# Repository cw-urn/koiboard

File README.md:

# koiboard
> What is this?
- Koiboard is a 40% ortholinear mechanical low-profile keyboard.
> How do you use it?
- Well you know how to you a keyboard, right? This one just has its keys aligned differently!
> Why did I make this?
- Honestly, I saw the simplicity of the [XYZ Work Board](https://worklouder.cc/xyz-work-board-2), plus other boards, and thought I could make it myself.

<hr>

<hr>

## 3D render

## PCB
[Open online PCB viewer](https://kicanvas.org/?repo=https%3A%2F%2Fgithub.com%2Fcw-urn%2Fkoiboard%2Ftree%2Fmain%2Fpcb)

### Layer 1

### Layer 2

### PCB 3D render

### Final PCB

### Schematic
This is split up into multiple pages. Check pcb/exports/koiboard.pdf!

## Gallery

More images in assets/webp!!!

## PCB BOM

| Designator | Quantity | Value | LCSC Part # | JLCPCB Link |
| :---: | :---: | :---: | :---: | :---: |
| BOOT1, RST1 | 2 | - | C455262 | [Link](https://jlcpcb.com/partdetail/XUNPU-TS_1087S01526/C455262) |
| C1, C2, C14 | 3 | 1u | C14445 | [Link](https://jlcpcb.com/partdetail/15107-CL05A105KP5NNNC/C14445) |
| C4...13 | 10 | 100n | C1525 | [Link](https://jlcpcb.com/partdetail/1877-CL05B104KO5NNNC/C1525) |
| C15, C16 | 2 | 33p | C1562 | [Link](https://jlcpcb.com/partdetail/1914-0402CG330J500NT/C1562) |
| C3 | 1 | 10u | C1691 | [Link](https://jlcpcb.com/partdetail/2043-CL10A106MQ8NNNC/C1691) |
| **D1...49** | 49 | - | C2099 | [Link](https://jlcpcb.com/partdetail/2456-1N4148W/C2099) |
| F1 | 1 | - | C99563 | [Link](https://jlcpcb.com/partdetail/Littelfuse-1206L075THYR/C99563) |
| J1 | 1 | - | C5370443 | [Link](https://jlcpcb.com/partdetail/Korean_HropartsElec-TYPE_C_31_M40/C5370443) |
| **R1...5** | 5 | 5.1k | C25905 | [Link](https://jlcpcb.com/partdetail/26648-0402WGF5101TCE/C25905) |
| R6, R9 | 2 | 1k | C11702 | [Link](https://jlcpcb.com/partdetail/12256-0402WGF1001TCE/C11702) |
| R7, R8 | 2 | 27 | C25100 | [Link](https://jlcpcb.com/partdetail/25843-0402WGF270JTCE/C25100) |
| U1 | 1 | - | C5446 | [Link](https://jlcpcb.com/partdetail/TorexSemicon-XC6206P332MRG/C5446) |
| U2 | 1 | - | C7519 | [Link](https://jlcpcb.com/partdetail/STMicroelectronics-USBLC62SC6/C7519) |
| U3 | 1 | - | C2040 | [Link](https://jlcpcb.com/partdetail/RaspberryPi-RP2040/C2040) |
| U4 | 1 | - | C97521 | [Link](https://jlcpcb.com/partdetail/WinbondElec-W25Q128JVSIQ/C97521) |
| Y1 | 1 | - | C20625731 | [Link](https://jlcpcb.com/partdetail/AbraconLLC-ABM8_272T3/C20625731) |

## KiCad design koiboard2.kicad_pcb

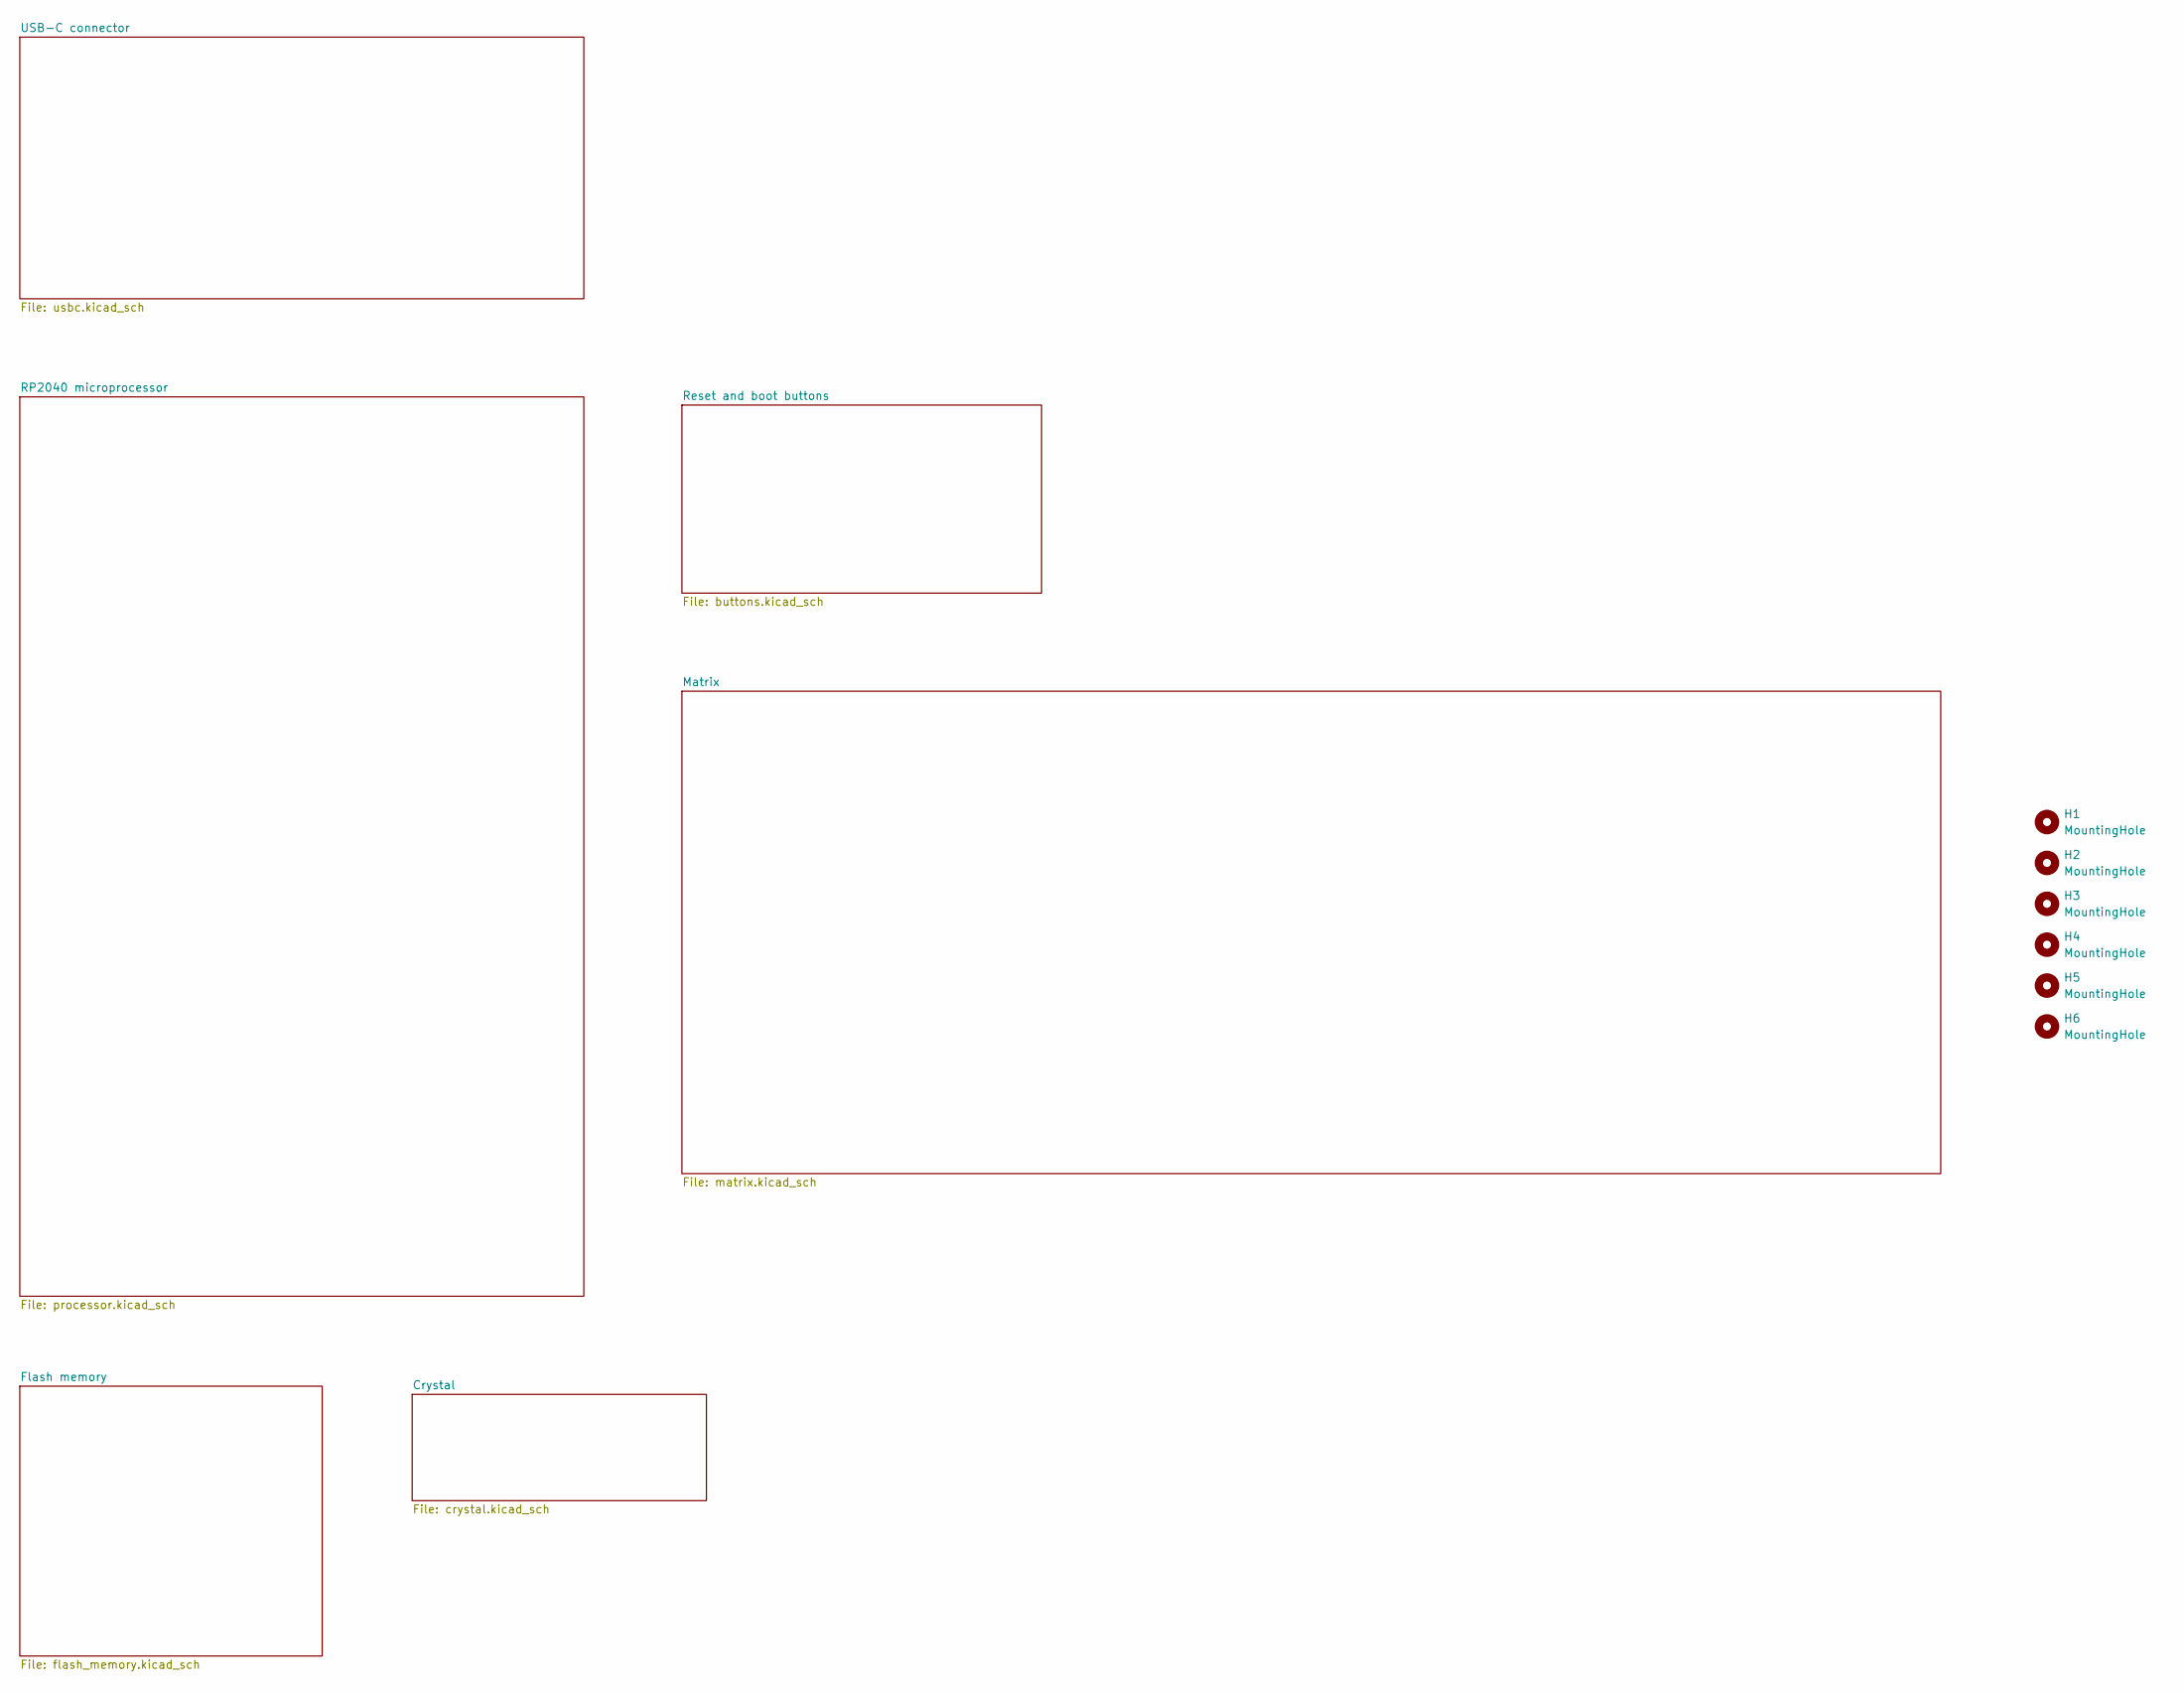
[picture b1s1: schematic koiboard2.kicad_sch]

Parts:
H1, H2, H3, H4, H5, H6: MountingHole; MountingHole_3.2mm_M3_ISO14580

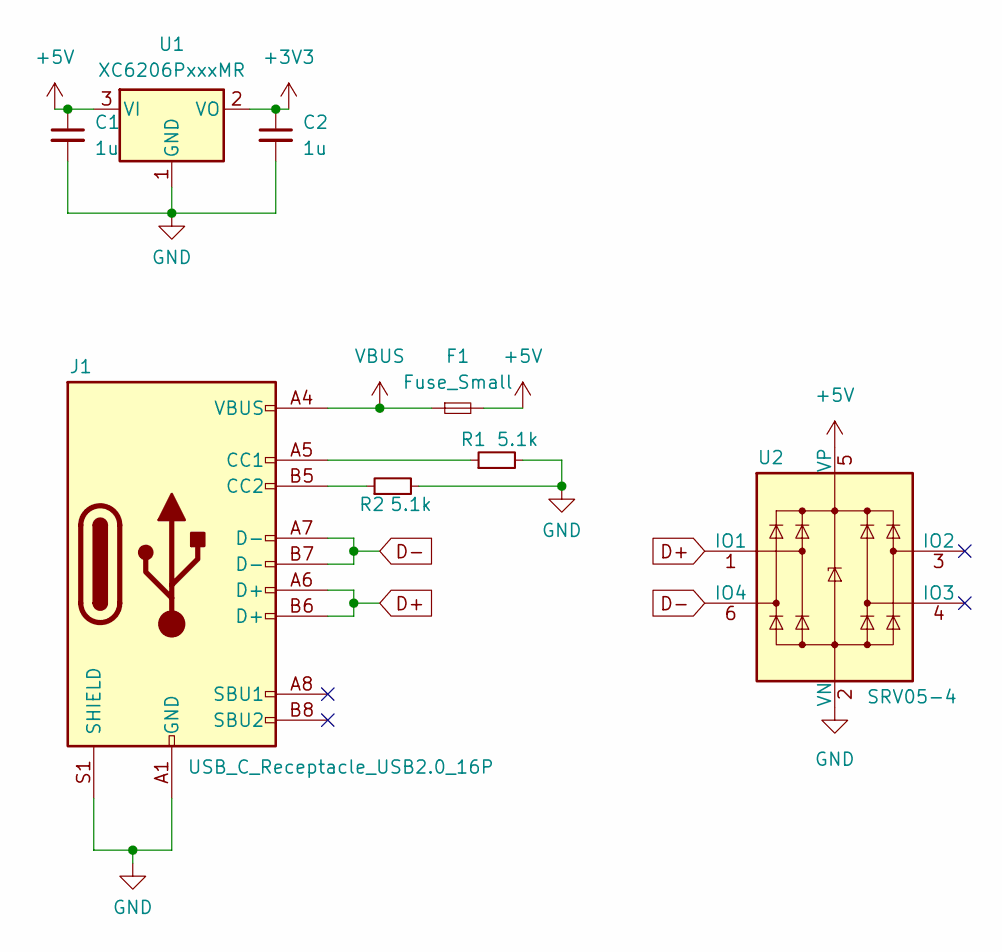
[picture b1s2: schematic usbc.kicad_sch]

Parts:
C1, C2: 1u; C_0402_1005Metric; LCSC C14445
F1: Fuse_Small; Fuse_1206_3216Metric; LCSC C99563
J1: USB_C_Receptacle_USB2.0_16P; USB_C_Receptacle_HRO_TYPE-C-31-M-12; LCSC C5370443
R1, R2: 5.1k; R_0402_1005Metric; LCSC C25905
U1: XC6206PxxxMR; SOT-23-3; LCSC C5446
U2: SRV05-4; SOT-23-6-routable; LCSC C7519

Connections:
+3V3: C2.1, U1.2 (VO); also elsewhere on the board
+5V: C1.1, F1.2, U1.3 (VI), U2.5 (VP)
D+: J1.A6 (D+), J1.B6 (D+), U2.1 (IO1); also elsewhere on the board
D-: J1.A7 (D-), J1.B7 (D-), U2.6 (IO4); also elsewhere on the board
GND: C1.2, C2.2, J1.A1 (GND), J1.A12 (GND), J1.B1 (GND), J1.B12 (GND), J1.S1 (SHIELD), R1.2, R2.2, U1.1 (GND), U2.2 (VN); also elsewhere on the board
unnamed: J1.A5 (CC1), R1.1
unnamed: J1.B5 (CC2), R2.1
VBUS: F1.1, J1.A4 (VBUS), J1.A9 (VBUS), J1.B4 (VBUS), J1.B9 (VBUS)

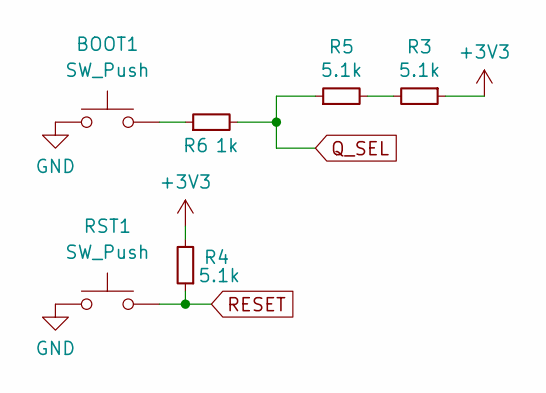
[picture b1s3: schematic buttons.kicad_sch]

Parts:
BOOT1: SW_Push; SW_SPST_TL3342; LCSC C455262
R3, R4, R5: 5.1k; R_0402_1005Metric; LCSC C25905
R6: 1k; R_0402_1005Metric; LCSC C11702
RST1: SW_Push; SW_SPST_TL3342; LCSC C455262

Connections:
+3V3: R3.1, R4.2; also elsewhere on the board
GND: BOOT1.1, RST1.1; also elsewhere on the board
unnamed: BOOT1.2, R6.1
unnamed: R3.2, R5.2
Q_SEL: R5.1, R6.2; also elsewhere on the board
RESET: R4.1, RST1.2; also elsewhere on the board

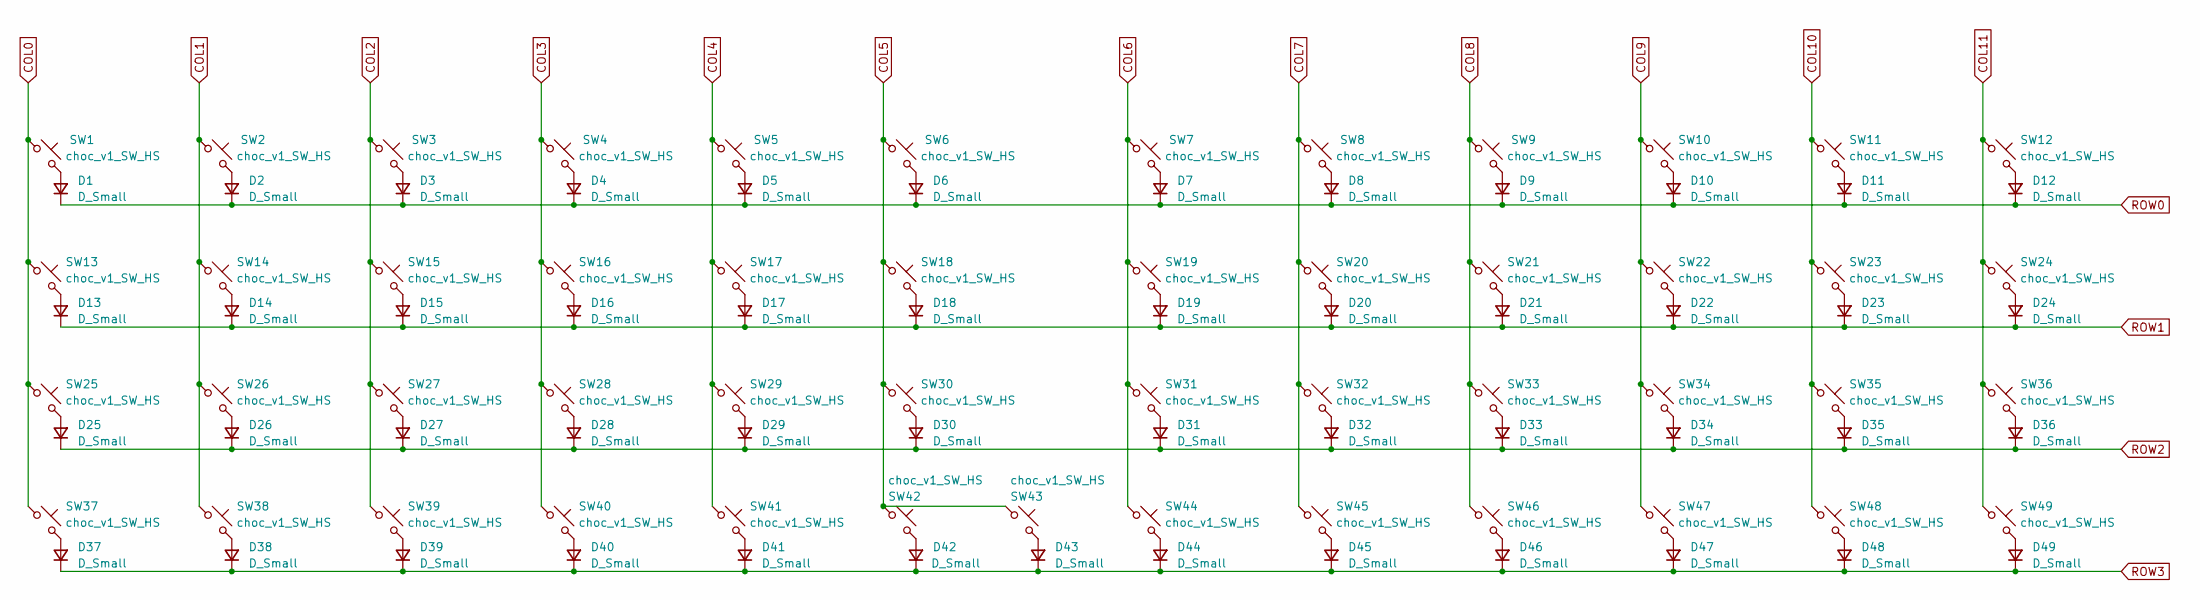
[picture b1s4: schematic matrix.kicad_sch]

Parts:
D1, D2, D3, D4, D5, D6, D7, D8, D9, D10, D11, D12, D13, D14, D15, D16, D17, D18, D19, D20, D21, D22, D23, D24, D25, D26, D27, D28, D29, D30, D31, D32, D33, D34, D35, D36, D37, D38, D39, D40, D41, D42, D43, D44, D45, D46, D47, D48, D49: D_Small; D_SOD-123
SW1, SW2, SW3, SW4, SW5, SW6, SW7, SW8, SW9, SW10, SW11, SW12, SW13, SW14, SW15, SW16, SW17, SW18, SW19, SW20, SW21, SW22, SW23, SW24, SW25, SW26, SW27, SW28, SW29, SW30, SW31, SW32, SW33, SW34, SW35, SW36, SW37, SW38, SW39, SW40, SW41, SW45, SW46, SW47, SW48, SW49: choc_v1_SW_HS; SW_choc_v2_HS_CPG135001S30_1u
SW42: choc_v1_SW_HS; SW_choc_v2_HS_CPG135001S30_1u_SW42
SW43: choc_v1_SW_HS; SW_choc_v2_HS_CPG135001S30_1u_SW42_switch_show
SW44: choc_v1_SW_HS; SW_choc_v2_HS_CPG135001S30_1u_switch_hide

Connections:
COL0: SW1.1, SW13.1, SW25.1, SW37.1; also elsewhere on the board
COL1: SW2.1, SW14.1, SW26.1, SW38.1; also elsewhere on the board
COL2: SW3.1, SW15.1, SW27.1, SW39.1; also elsewhere on the board
COL3: SW4.1, SW16.1, SW28.1, SW40.1; also elsewhere on the board
COL4: SW5.1, SW17.1, SW29.1, SW41.1; also elsewhere on the board
COL5: SW6.1, SW18.1, SW30.1, SW42.1, SW43.1; also elsewhere on the board
COL6: SW7.1, SW19.1, SW31.1, SW44.1; also elsewhere on the board
COL7: SW8.1, SW20.1, SW32.1, SW45.1; also elsewhere on the board
COL8: SW9.1, SW21.1, SW33.1, SW46.1; also elsewhere on the board
COL9: SW10.1, SW22.1, SW34.1, SW47.1; also elsewhere on the board
COL10: SW11.1, SW23.1, SW35.1, SW48.1; also elsewhere on the board
COL11: SW12.1, SW24.1, SW36.1, SW49.1; also elsewhere on the board
unnamed: D1.2 (A), SW1.2
unnamed: D2.2 (A), SW2.2
unnamed: D3.2 (A), SW3.2
unnamed: D4.2 (A), SW4.2
unnamed: D5.2 (A), SW5.2
unnamed: D6.2 (A), SW6.2
unnamed: D7.2 (A), SW7.2
unnamed: D8.2 (A), SW8.2
unnamed: D9.2 (A), SW9.2
unnamed: D10.2 (A), SW10.2
unnamed: D11.2 (A), SW11.2
unnamed: D12.2 (A), SW12.2
unnamed: D13.2 (A), SW13.2
unnamed: D14.2 (A), SW14.2
unnamed: D15.2 (A), SW15.2
unnamed: D16.2 (A), SW16.2
unnamed: D17.2 (A), SW17.2
unnamed: D18.2 (A), SW18.2
unnamed: D19.2 (A), SW19.2
unnamed: D20.2 (A), SW20.2
unnamed: D21.2 (A), SW21.2
unnamed: D22.2 (A), SW22.2
unnamed: D23.2 (A), SW23.2
unnamed: D24.2 (A), SW24.2
unnamed: D25.2 (A), SW25.2
unnamed: D26.2 (A), SW26.2
unnamed: D27.2 (A), SW27.2
unnamed: D28.2 (A), SW28.2
unnamed: D29.2 (A), SW29.2
unnamed: D30.2 (A), SW30.2
unnamed: D31.2 (A), SW31.2
unnamed: D32.2 (A), SW32.2
unnamed: D33.2 (A), SW33.2
unnamed: D34.2 (A), SW34.2
unnamed: D35.2 (A), SW35.2
unnamed: D36.2 (A), SW36.2
unnamed: D37.2 (A), SW37.2
unnamed: D38.2 (A), SW38.2
unnamed: D39.2 (A), SW39.2
unnamed: D40.2 (A), SW40.2
unnamed: D41.2 (A), SW41.2
unnamed: D42.2 (A), SW42.2
unnamed: D43.2 (A), SW43.2
unnamed: D44.2 (A), SW44.2
unnamed: D45.2 (A), SW45.2
unnamed: D46.2 (A), SW46.2
unnamed: D47.2 (A), SW47.2
unnamed: D48.2 (A), SW48.2
unnamed: D49.2 (A), SW49.2
ROW0: D1.1 (K), D2.1 (K), D3.1 (K), D4.1 (K), D5.1 (K), D6.1 (K), D7.1 (K), D8.1 (K), D9.1 (K), D10.1 (K), D11.1 (K), D12.1 (K); also elsewhere on the board
ROW1: D13.1 (K), D14.1 (K), D15.1 (K), D16.1 (K), D17.1 (K), D18.1 (K), D19.1 (K), D20.1 (K), D21.1 (K), D22.1 (K), D23.1 (K), D24.1 (K); also elsewhere on the board
ROW2: D25.1 (K), D26.1 (K), D27.1 (K), D28.1 (K), D29.1 (K), D30.1 (K), D31.1 (K), D32.1 (K), D33.1 (K), D34.1 (K), D35.1 (K), D36.1 (K); also elsewhere on the board
ROW3: D37.1 (K), D38.1 (K), D39.1 (K), D40.1 (K), D41.1 (K), D42.1 (K), D43.1 (K), D44.1 (K), D45.1 (K), D46.1 (K), D47.1 (K), D48.1 (K), D49.1 (K); also elsewhere on the board

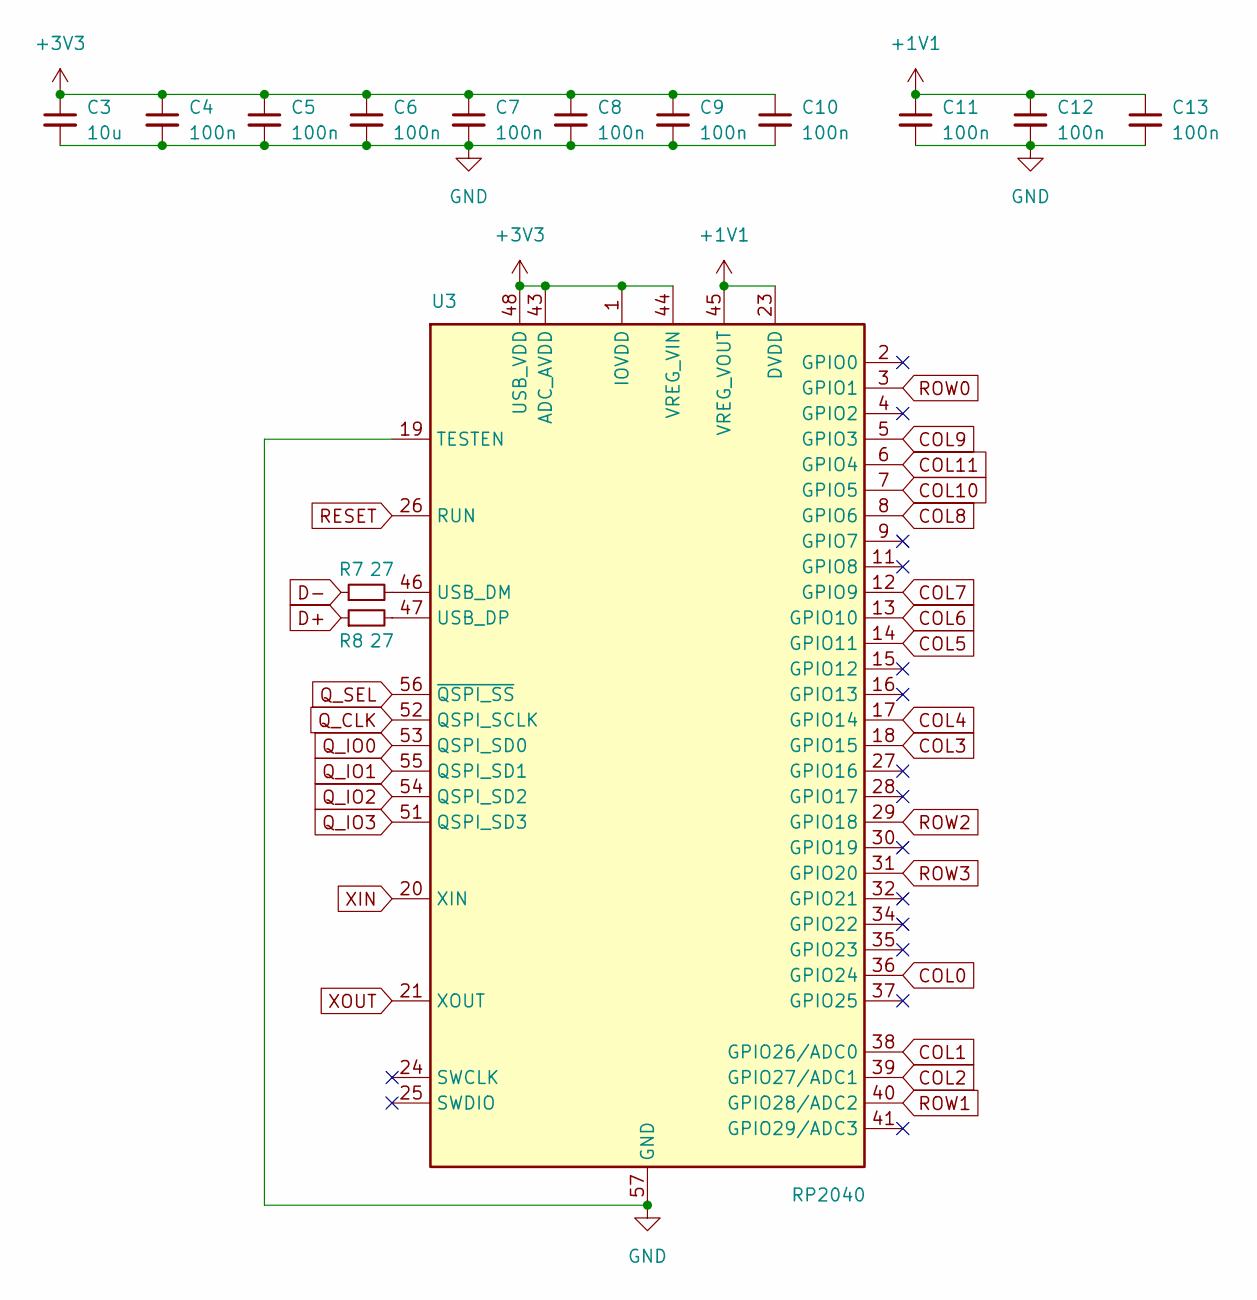
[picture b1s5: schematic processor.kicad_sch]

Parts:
C3: 10u; C_0603_1608Metric; LCSC C1691
C4, C5, C6, C7, C8, C9, C10, C11, C12, C13: 100n; C_0402_1005Metric; LCSC C1525
R7, R8: 27; R_0402_1005Metric; LCSC C25100
U3: RP2040; QFN-56-1EP_7x7mm_P0.4mm_EP3.2x3.2mm; LCSC C2040

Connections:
+1V1: C11.1, C12.1, C13.1, U3.23 (DVDD), U3.45 (VREG_VOUT), U3.50 (DVDD)
+3V3: C3.1, C4.1, C5.1, C6.1, C7.1, C8.1, C9.1, C10.1, U3.1 (IOVDD), U3.10 (IOVDD), U3.22 (IOVDD), U3.33 (IOVDD), U3.42 (IOVDD), U3.43 (ADC_AVDD), U3.44 (VREG_VIN), U3.48 (USB_VDD), U3.49 (IOVDD); also elsewhere on the board
COL0: U3.36 (GPIO24); also elsewhere on the board
COL1: U3.38 (GPIO26/ADC0); also elsewhere on the board
COL2: U3.39 (GPIO27/ADC1); also elsewhere on the board
COL3: U3.18 (GPIO15); also elsewhere on the board
COL4: U3.17 (GPIO14); also elsewhere on the board
COL5: U3.14 (GPIO11); also elsewhere on the board
COL6: U3.13 (GPIO10); also elsewhere on the board
COL7: U3.12 (GPIO9); also elsewhere on the board
COL8: U3.8 (GPIO6); also elsewhere on the board
COL9: U3.5 (GPIO3); also elsewhere on the board
COL10: U3.7 (GPIO5); also elsewhere on the board
COL11: U3.6 (GPIO4); also elsewhere on the board
D+: R8.1; also elsewhere on the board
D-: R7.1; also elsewhere on the board
GND: C3.2, C4.2, C5.2, C6.2, C7.2, C8.2, C9.2, C10.2, C11.2, C12.2, C13.2, U3.19 (TESTEN), U3.57 (GND); also elsewhere on the board
unnamed: R7.2, U3.46 (USB_DM)
unnamed: R8.2, U3.47 (USB_DP)
Q_CLK: U3.52 (QSPI_SCLK); also elsewhere on the board
Q_IO0: U3.53 (QSPI_SD0); also elsewhere on the board
Q_IO1: U3.55 (QSPI_SD1); also elsewhere on the board
Q_IO2: U3.54 (QSPI_SD2); also elsewhere on the board
Q_IO3: U3.51 (QSPI_SD3); also elsewhere on the board
Q_SEL: U3.56 (~QSPI_SS); also elsewhere on the board
RESET: U3.26 (RUN); also elsewhere on the board
ROW0: U3.3 (GPIO1); also elsewhere on the board
ROW1: U3.40 (GPIO28/ADC2); also elsewhere on the board
ROW2: U3.29 (GPIO18); also elsewhere on the board
ROW3: U3.31 (GPIO20); also elsewhere on the board
XIN: U3.20 (XIN); also elsewhere on the board
XOUT: U3.21 (XOUT); also elsewhere on the board

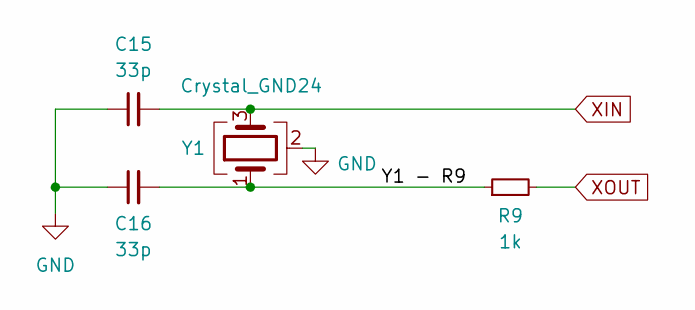
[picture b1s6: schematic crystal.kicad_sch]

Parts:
C15, C16: 33p; C_0402_1005Metric; LCSC C1562
R9: 1k; R_0402_1005Metric; LCSC C11702
Y1: Crystal_GND24; Crystal_SMD_3225-4Pin_3.2x2.5mm; LCSC C20625731

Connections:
/Crystal/Y1 - R9: C16.2, R9.1, Y1.1
GND: C15.1, C16.1, Y1.2 (G), Y1.4 (G); also elsewhere on the board
XIN: C15.2, Y1.3; also elsewhere on the board
XOUT: R9.2; also elsewhere on the board

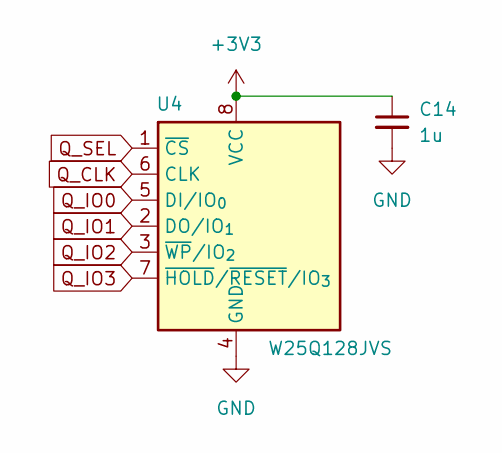
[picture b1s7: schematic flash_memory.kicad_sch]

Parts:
C14: 1u; C_0402_1005Metric; LCSC C14445
U4: W25Q128JVS; SOIC-8_5.3x5.3mm_P1.27mm; LCSC C97521

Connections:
+3V3: C14.1, U4.8 (VCC); also elsewhere on the board
GND: C14.2, U4.4 (GND); also elsewhere on the board
Q_CLK: U4.6 (CLK); also elsewhere on the board
Q_IO0: U4.5 (DI/IO_{0}); also elsewhere on the board
Q_IO1: U4.2 (DO/IO_{1}); also elsewhere on the board
Q_IO2: U4.3 (~WP/IO_{2}); also elsewhere on the board
Q_IO3: U4.7 (~HOLD/~RESET/IO_{3}); also elsewhere on the board
Q_SEL: U4.1 (~CS); also elsewhere on the board

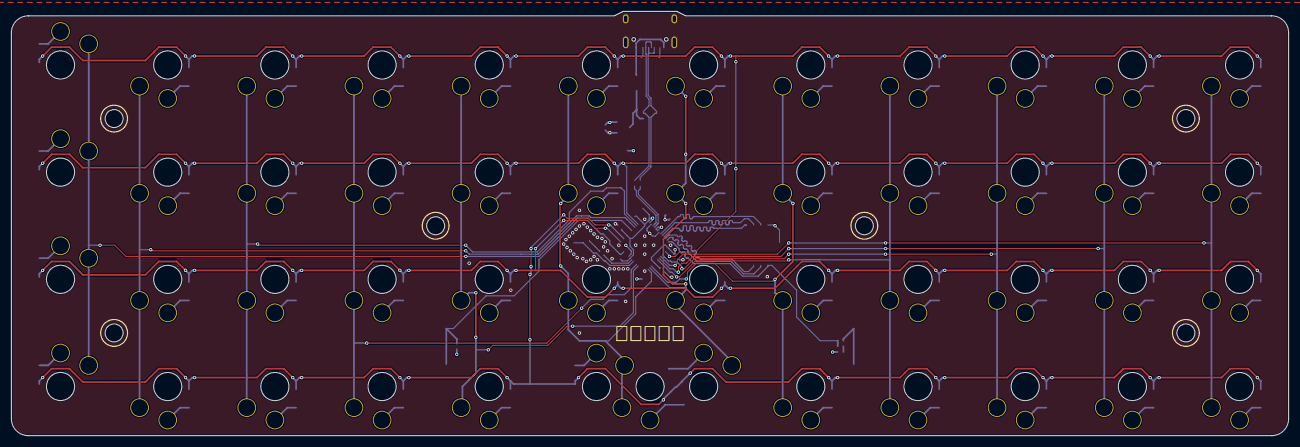
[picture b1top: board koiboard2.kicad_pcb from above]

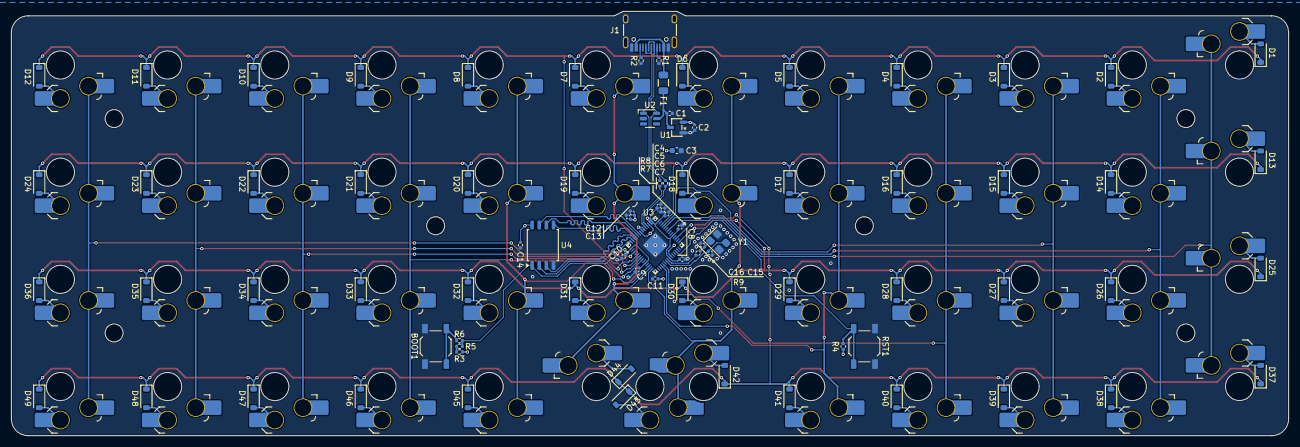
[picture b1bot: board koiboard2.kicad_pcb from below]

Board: 4 copper layers, 227.0 x 75.4 mm, 138 parts (132 on the bottom side), 88 nets.

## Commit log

2026-02-06 Add Koiboard2 KiCad project and gerbers
    Add the full Koiboard2 KiCad project and generated fabrication artifacts. Files added include .kicad_pro, .kicad_sch, .kicad_pcb, fabrication-toolkit options, keyautoplace log, production backups/zip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
2026-02-07 silkscreen update
2026-02-09 update
    new 3d files, stab removed, logo moved, 2x1u <-> 2u support, cleanup, pcb dxf, ect...
2026-02-15 added 3 switches for the space bar
2026-02-15 added usbc connector 3d model
2026-02-15 created 2D plate design and exported that into an svg
2026-02-26 update from review
2026-03-07 4 layers
2026-03-12 routed matrix
2026-03-13 drc errors fix
2026-03-24 idk bom stuff
2026-03-30 final(?) update
2026-03-30 Rename final.PNG to final.png
2026-03-30 schematic
2026-03-30 ultra readme update
    big
2026-04-08 update alt
2026-04-10 2 layer final
2026-04-10 readme update 3
2026-05-26 final
2026-05-26 read me
